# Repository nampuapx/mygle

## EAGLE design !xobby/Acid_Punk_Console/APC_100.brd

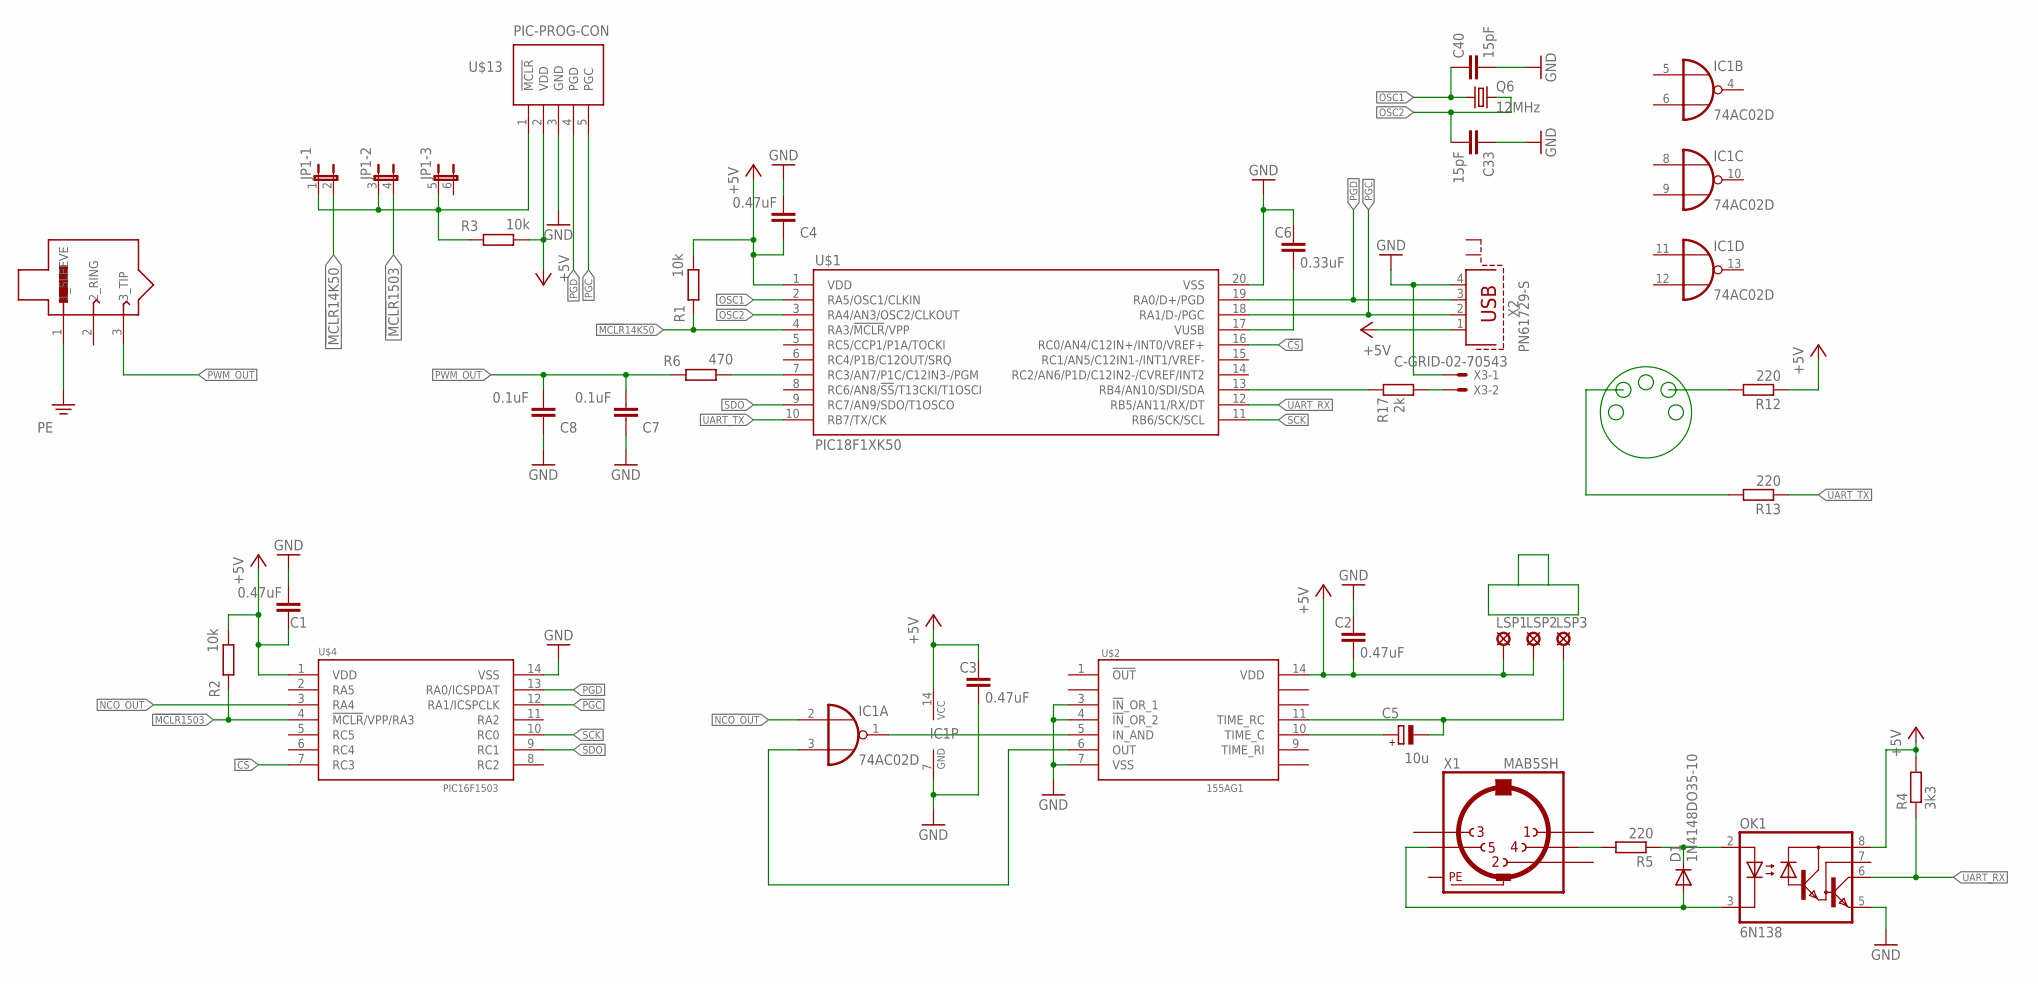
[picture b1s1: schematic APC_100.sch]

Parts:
C1, C2, C3, C4: 0.47uF; C1206
C5: 10u; CT3528
C6: 0.33uF; C1206
C7, C8: 0.1uF; C1206
C33, C40: 15pF; C1206
D1: 1N4148DO35-10; DO35-10
IC1: 74AC02D; SO14
JP1: JP3QE; JP3Q
LSP1, LSP2, LSP3: SE13
OK1: 6N138; DIL08
Q6: 12MHz; HC49/S
R1, R2, R3: 10k; M1206
R4: 3k3; M1206
R5, R12, R13: 220; M1206
R6: 470; M1206
R17: 2k; M1206
U$1: PIC18F1XK50; SOIC20
U$2: 155AG1; DIP14
U$3: STEREO_JACK_6.3; JACK6.3_MAMA_STEREO
U$4: PIC16F1503; SO14
U$13: PIC-PROG-CON
X1: MAB5SH
X2: PN61729-S
X3: C-GRID-02-70543; 70543-02

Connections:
!CS: U$1.16 (RC0/AN4/C12IN+/INT0/VREF+), U$4.7 (RC3)
!MCLR!14K50: JP1.2, R1.1, U$1.4 (RA3/!MCLR!/VPP)
!MCLR!1503: JP1.4 (2), R2.1, U$4.4 (!MCLR!/VPP/RA3)
+5V: C1.2, C2.1, C3.2, C4.2, IC1.14 (VCC), LSP1.MP, LSP2.MP, OK1.8 (VCC), R1.2, R2.2, R3.2, R4.2, R12.1, U$1.1 (VDD), U$2.14 (VDD), U$4.1 (VDD), U$13.2 (VDD), X2.1
FIRST_SOUND: IC1.1 (O), U$2.5 (IN_AND)
GND: C1.1, C2.2, C3.1, C4.1, C6.2, C7.2, C8.2, C33.1, C40.2, IC1.7 (GND), OK1.5 (GND), U$1.20 (VSS), U$2.3 (!IN!_OR_1), U$2.4 (!IN!_OR_2), U$2.7 (VSS), U$4.14 (VSS), U$13.3 (GND), X2.4, X3.1
MCLR: JP1.1, JP1.3 (1), JP1.5 (1), R3.1, U$13.1 (!MCLR)
unnamed: C5.+, U$2.10 (TIME_C)
unnamed: IC1.3 (I1), U$2.6 (OUT)
unnamed: C5.-, LSP3.MP, U$2.11 (TIME_RC)
unnamed: D1.C, OK1.2 (A), R5.1
unnamed: R5.2, X1.4
unnamed: D1.A, OK1.3 (C), X1.5
unnamed: C6.1, U$1.17 (VUSB)
unnamed: R17.1, X3.2
unnamed: R17.2, U$1.13 (RB4/AN10/SDI/SDA)
unnamed: R6.2, U$1.7 (RC3/AN7/P1C/C12IN3-/PGM)
NCO_OUT: IC1.2 (I0), U$4.3 (RA4)
OSC1: C40.1, Q6.1, U$1.2 (RA5/OSC1/CLKIN)
OSC2: C33.2, Q6.2, U$1.3 (RA4/AN3/OSC2/CLKOUT)
PE: U$3.1 (1_SLEEVE), X1.PE, X1.PE@ (PE)
PGC: U$1.18 (RA1/D-/PGC), U$4.12 (RA1/ICSPCLK), U$13.5 (PGC), X2.2
PGD: U$1.19 (RA0/D+/PGD), U$4.13 (RA0/ICSPDAT), U$13.4 (PGD), X2.3
PWM_OUT: C7.1, C8.1, R6.1, U$3.3 (3_TIP)
SCK: U$1.11 (RB6/SCK/SCL), U$4.10 (RC0)
SDO: U$1.9 (RC7/AN9/SDO/T1OSCO), U$4.9 (RC1)
UART_RX: OK1.6 (VO), R4.1, U$1.12 (RB5/AN11/RX/DT)
UART_TX: R13.1, U$1.10 (RB7/TX/CK)

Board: 2 copper layers, 35 parts (4 on the bottom side), 28 nets, no tracks yet.

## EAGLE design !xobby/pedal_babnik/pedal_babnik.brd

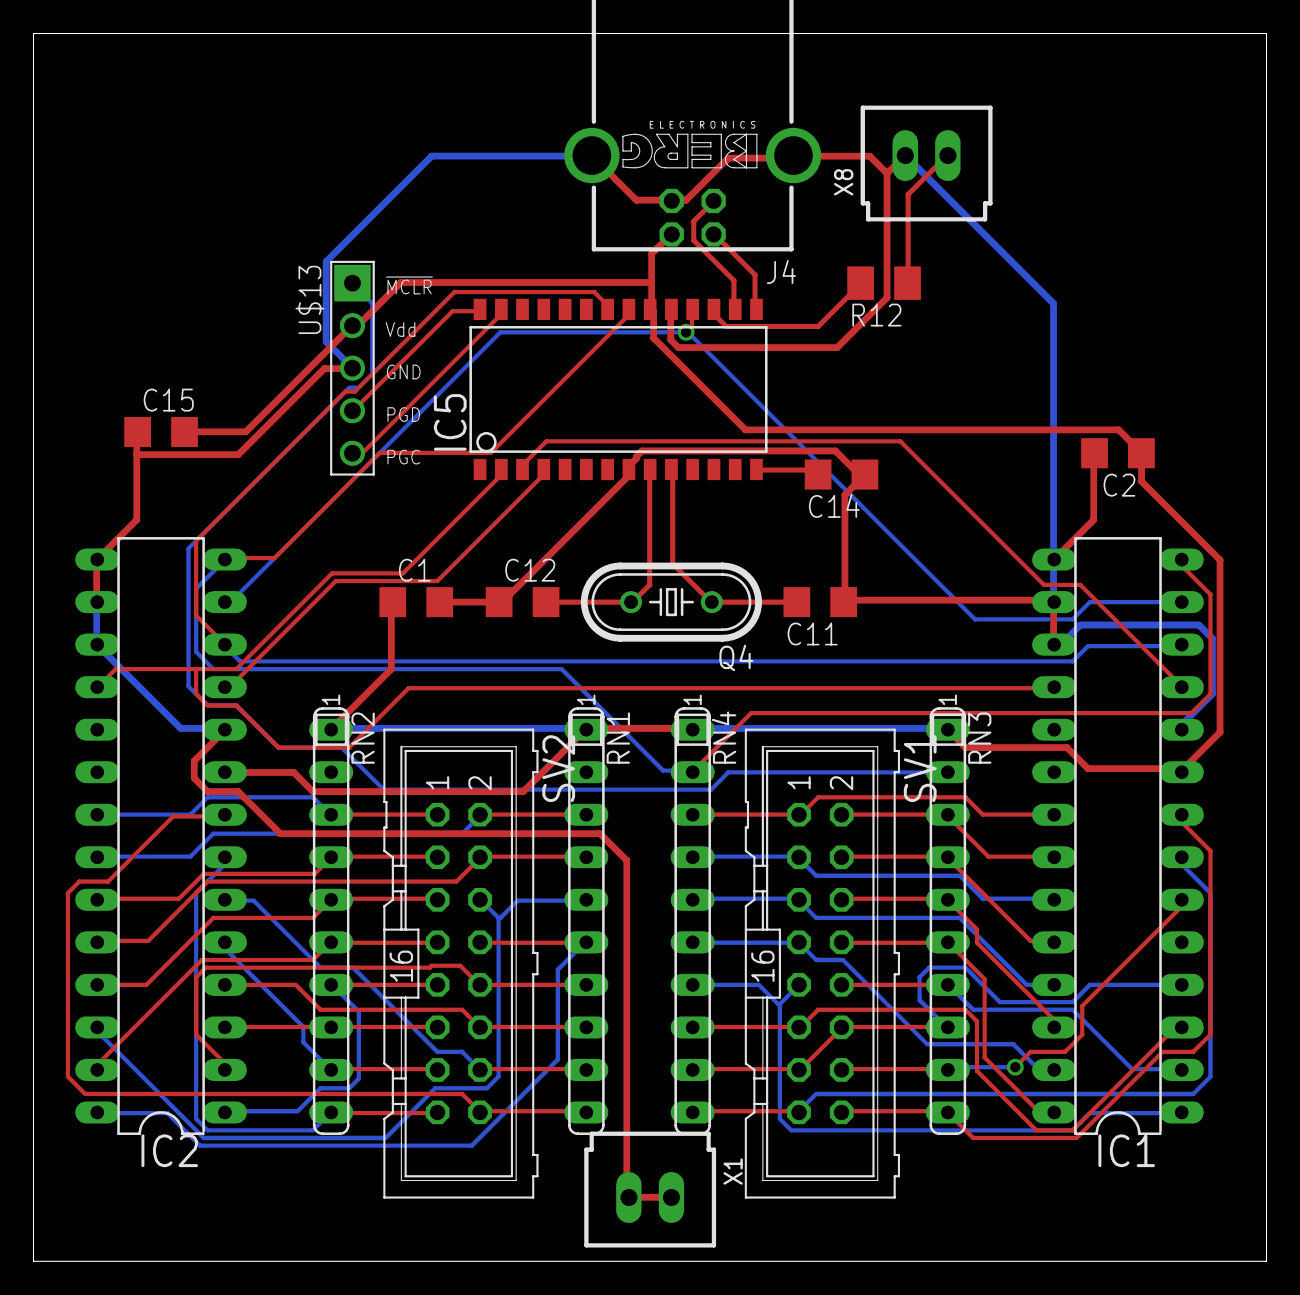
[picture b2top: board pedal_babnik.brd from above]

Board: 2 copper layers, 73.6 x 73.3 mm, 21 parts (0 on the bottom side), 49 nets.

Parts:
C1, C2, C15: 0.1u; C1206
C11, C12: 15pF; C1206
C14: 0.47u; C1206
IC1, IC2: MCP23S17SP; DIL28-3
IC5: PIC18F2550_28W; SO28W
J4: PN61729-S
Q4: HC49/S
R12: 5.1k; M1206
RN1, RN2, RN3, RN4: SIL10
SV1, SV2: ML16
U$13: PIC-PROG-CON
X1, X8: C-GRID-02-70543; 70543-02

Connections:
CS_N1: IC1.11, IC5.3
CS_N2: IC2.11, IC5.4
GND: C1.2, C2.2, C11.1, C12.1, C14.1, C15.1, IC1.10, IC1.15, IC1.16, IC1.17, IC2.10, IC2.15, IC2.16, IC2.17, IC5.8, IC5.19, J4.4, J4.S1, J4.S2, U$13.3, X1.1, X1.2, X8.1
MCLR: RN3.2, U$13.1
unnamed: C12.2, IC5.9, Q4.2
unnamed: C11.2, IC5.10, Q4.1
unnamed: C14.2, IC5.14
unnamed: IC5.15, J4.2
unnamed: IC5.16, J4.3
unnamed: IC5.17, R12.2
unnamed: R12.1, X8.2
PE00: IC1.21, RN4.3, SV1.1
PE01: IC1.22, RN3.3, SV1.2
PE02: IC1.23, RN4.4, SV1.3
PE03: IC1.24, RN3.4, SV1.4
PE04: IC1.25, RN4.5, SV1.5
PE05: IC1.26, RN3.5, SV1.6
PE06: IC1.27, RN4.6, SV1.7
PE07: IC1.28, RN3.6, SV1.8
PE08: IC1.1, RN4.7, SV1.9
PE09: IC1.2, RN3.7, SV1.10
PE10: IC1.3, RN4.8, SV1.11
PE11: IC1.4, RN3.8, RN4.9, SV1.12, SV1.13
PE13: IC1.6, RN3.9, SV1.14
PE14: IC1.7, RN4.10, SV1.15
PE15: IC1.8, RN3.10, SV1.16
PE200: IC2.21, RN2.3, SV2.1
PE201: IC2.22, RN1.3, SV2.2
PE202: IC2.23, RN2.4, SV2.3
PE203: IC2.24, RN1.4, SV2.4
PE204: IC2.25, RN2.5, SV2.5
PE205: IC2.26, RN1.5, SV2.6
PE206: IC2.27, RN2.6, SV2.7
PE207: IC2.28, RN1.6, SV2.8
PE208: IC2.1, RN2.7, SV2.9
PE209: IC2.2, RN1.7, SV2.10
PE210: IC2.3, RN2.8, SV2.11
PE211: IC2.4, RN1.8, SV2.12
PE212: IC2.5, RN2.9, SV2.13
PE213: IC2.6, RN1.9, SV2.14
PE214: IC2.7, RN2.10, SV2.15
PE215: IC2.8, RN1.10, SV2.16
RESET_OUT: IC1.18, IC2.18, IC5.2
SCK: IC1.12, IC2.12, IC5.22
SDI: IC1.14, IC2.14, IC5.21, RN4.2
SDO: IC1.13, IC2.13, IC5.18
UPR_K0: IC5.27, U$13.5
UPR_K1: IC5.28, U$13.4
VCC: C1.1, C2.1, C15.2, IC1.9, IC2.9, IC5.20, J4.1, RN1.1, RN2.1, RN3.1, RN4.1, U$13.2
